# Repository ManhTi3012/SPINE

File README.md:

# S.P.I.N.E
**Stackable Power Integration & Network Electronics**

# Overview
S.P.I.N.E. is a decentralized power distribution architecture that splits control, distribution, and protection into discrete, stackable modules. Offers control and monitor over individual power rails, telemetry via CAN bus, and fault protection like over current, over voltage(due to back EMF), emergency stop.

# System Architecture
The system is composed of three primary module types, functioning analogously to a biological nervous system:

## 1. Cortex (Main Control Unit)
The Cortex is responsible for high-level decision-making and external communication.

- Bus Monitoring: Continuously monitors the main bus voltage.

- Orchestration: Controls the state of all connected Vertebra modules via RS485.

- Telemetry: Send internal system data to the external robot controller via CAN Bus.

## 2. Vertebra (Power Distribution & Switching)
Each Vertebra acts as an intelligent Power Distribution Unit (PDU).

- Distribution: Takes 1 main input and splits it into 3 protected outputs.

- Protection Topology: Utilizes a back-to-back switching topology to enable full bidirectional cutoff.

- Soft Start: Integrated Precharge circuit to prevent inrush current spikes during startup.

- Sensing: Real-time current and voltage sensing on outputs.

- Fault Propagation:

  - Local: Can autonomously cut power upon detecting over-current events.
  
  - Global: A "Critical Fault" in one Vertebra triggers a system-wide shutdown to protect the rest of the hardware.

## 3. Disc (Brake Chopper)
A purely hardware-based protection module.

- Function: Dissipates dangerous back-EMF (voltage spikes) generated by motors during rapid deceleration.

- Mechanism: A fast analog comparator circuit to trigger a dump load when voltage exceeds a set threshold.

- Zero-Latency: No microcontroller or software intervention required; purely reactive hardware protection.

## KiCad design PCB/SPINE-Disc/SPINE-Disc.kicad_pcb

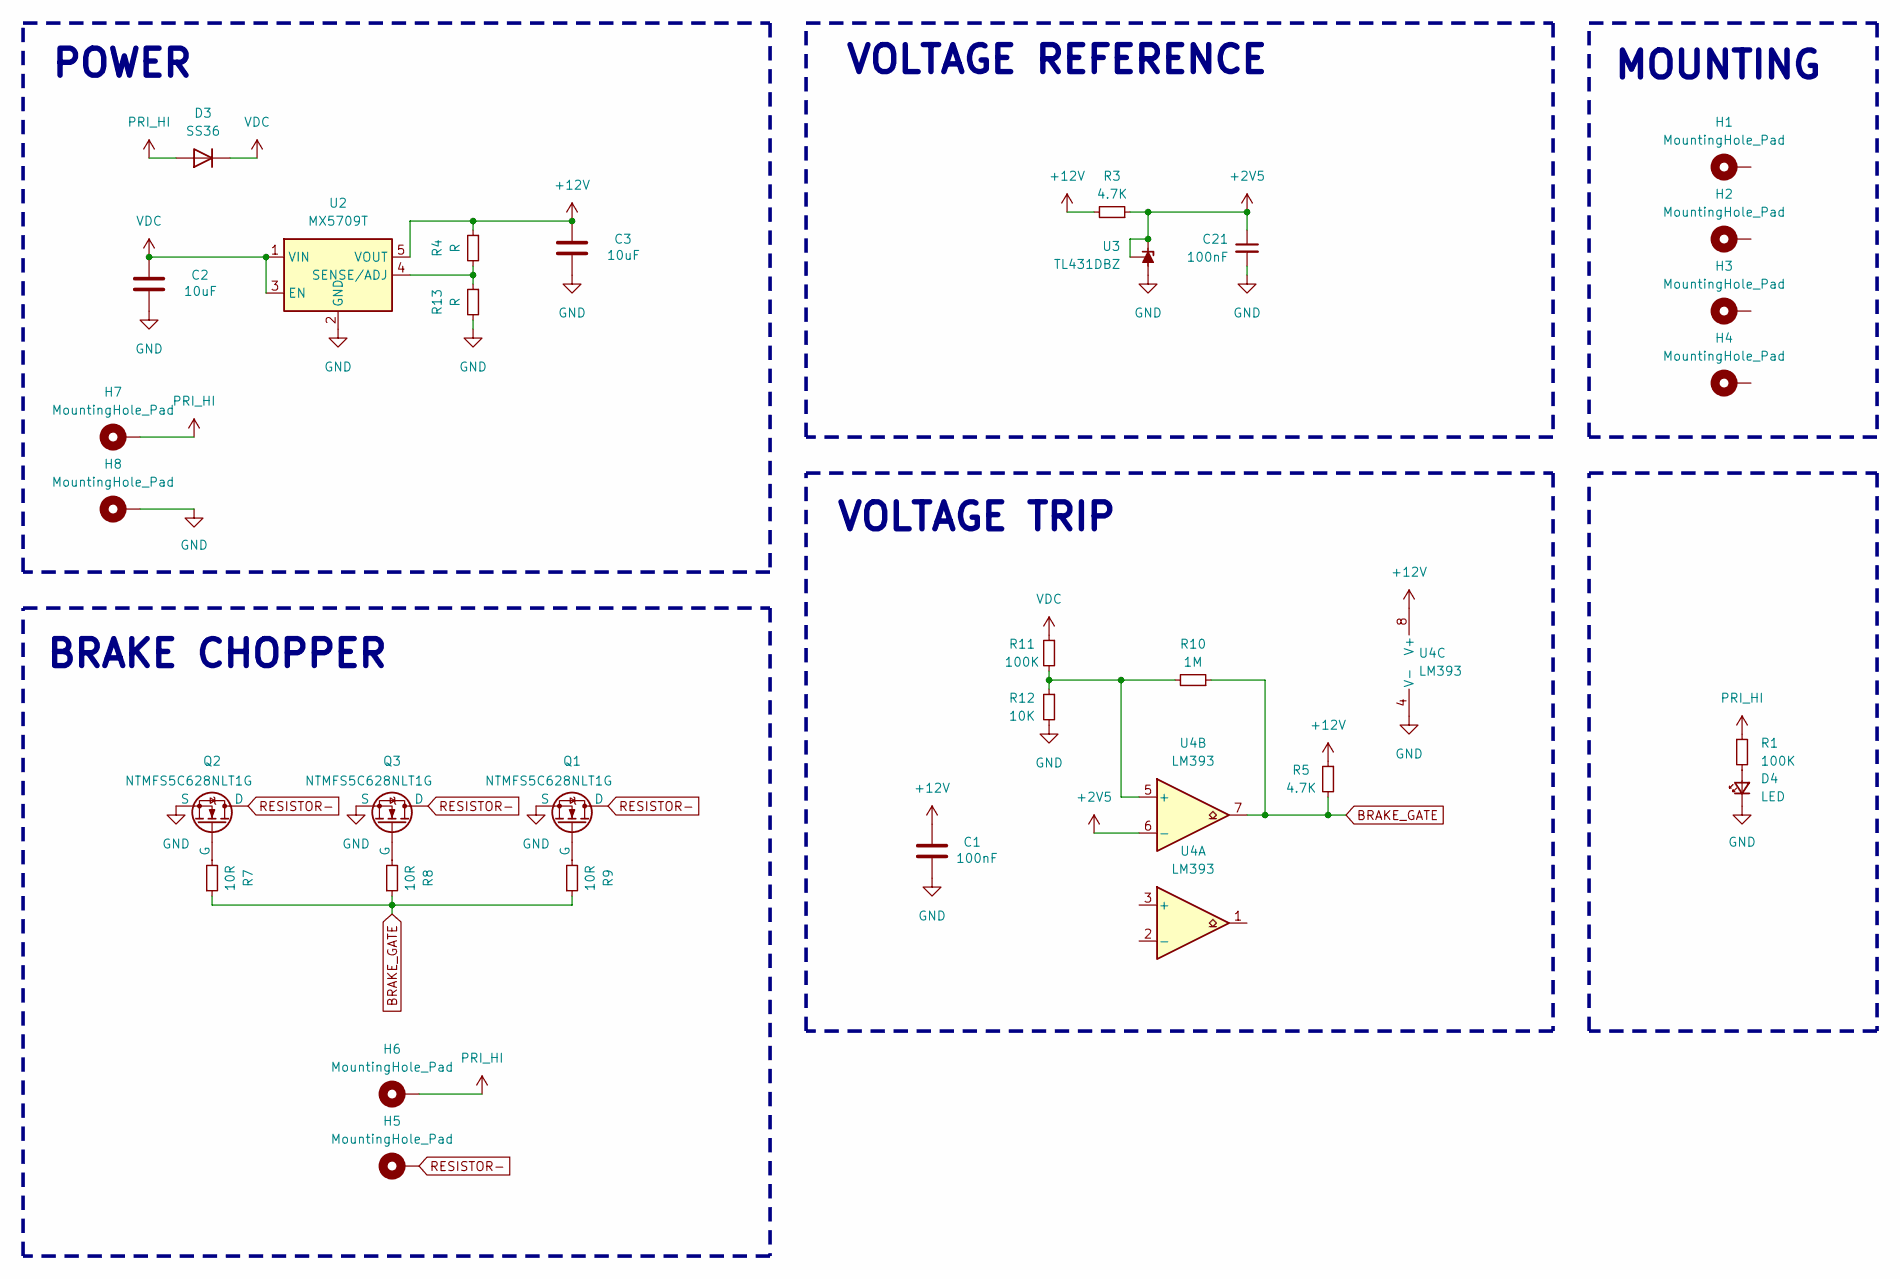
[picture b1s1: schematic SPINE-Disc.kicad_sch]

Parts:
C1: 100nF; C_0805_2012Metric
C2, C3: 10uF; C_1206_3216Metric
C21: 100nF; C_0603_1608Metric
D3: SS36; D_SMA
D4: LED; LED_0603_1608Metric
H1, H2, H3, H4, H5, H6, H7, H8: MountingHole_Pad; MountingHole_3.2mm_M3_Pad_Via
Q1, Q2, Q3: NTMFS5C628NLT1G; PQFN-8-EP_6x5mm_P1.27mm_Generic
R1, R11: 100K; R_0603_1608Metric
R3, R5: 4.7K; R_0603_1608Metric
R4, R13: R; R_0603_1608Metric
R7, R8, R9: 10R; R_0603_1608Metric
R10: 1M; R_0603_1608Metric
R12: 10K; R_0603_1608Metric
U2: MX5709T; TSOT-23-5
U3: TL431DBZ; SOT-23
U4: LM393; SOIC-8_3.9x4.9mm_P1.27mm

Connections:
+2V5: C21.1, R3.1, U3.1 (K), U3.2 (REF), U4.6 (-)
+12V: C1.2, C3.2, R3.2, R4.1, R5.1, U2.5 (VOUT), U4.8 (V+)
BRAKE_GATE: R5.2, R7.1, R8.1, R9.1, R10.1, U4.7
GND: C1.1, C2.1, C3.1, C21.2, D4.1 (K), H8.1, Q1.1 (S), Q1.2 (S), Q1.3 (S), Q2.1 (S), Q2.2 (S), Q2.3 (S), Q3.1 (S), Q3.2 (S), Q3.3 (S), R12.2, R13.2, U2.2 (GND), U3.3 (A), U4.4 (V-)
unnamed: D4.2 (A), R1.2
unnamed: Q1.4 (G), R9.2
unnamed: Q2.4 (G), R7.2
unnamed: Q3.4 (G), R8.2
unnamed: R4.2, R13.1, U2.4 (SENSE/ADJ)
unnamed: R10.2, R11.2, R12.1, U4.5 (+)
PRI_HI: D3.2 (A), H6.1, H7.1, R1.1
RESISTOR-: H5.1, Q1.5 (D), Q2.5 (D), Q3.5 (D)
VDC: C2.2, D3.1 (K), R11.1, U2.1 (VIN), U2.3 (EN)

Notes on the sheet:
VOLTAGE TRIP
VOLTAGE REFERENCE
POWER
BRAKE CHOPPER
MOUNTING

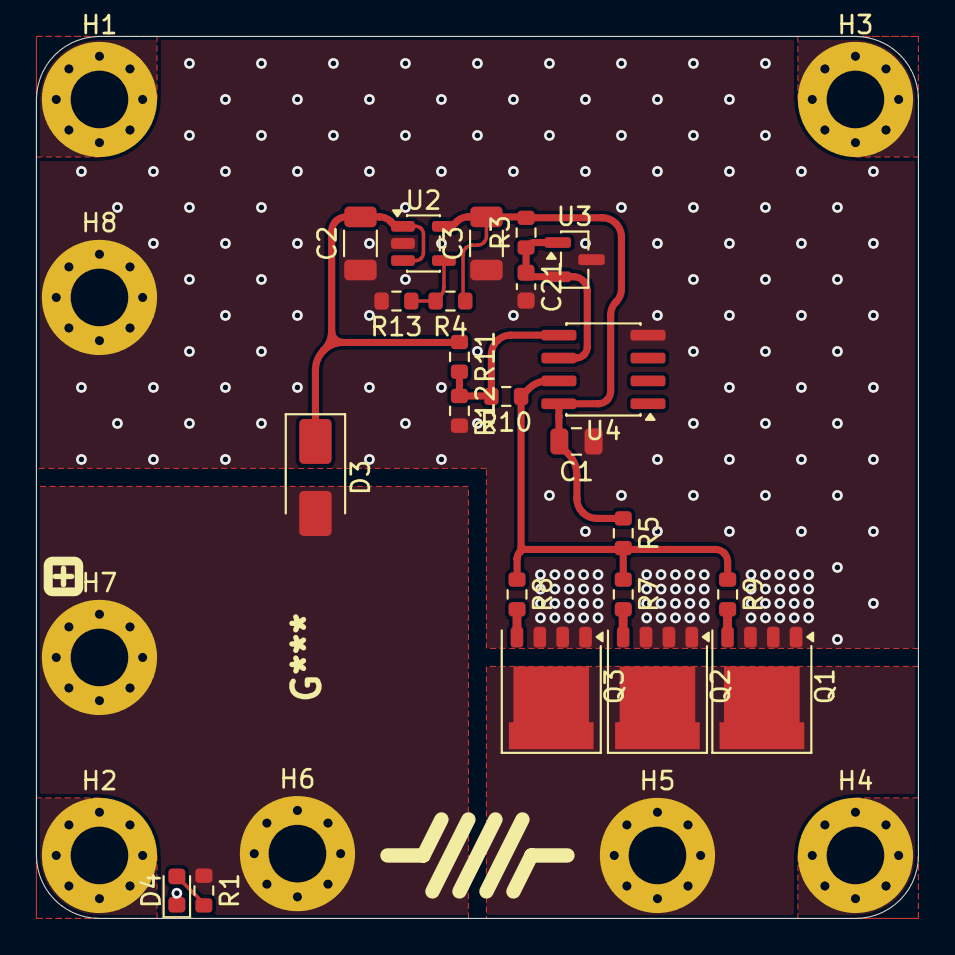
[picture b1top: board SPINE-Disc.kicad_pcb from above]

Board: 2 copper layers, 49.0 x 49.0 mm, 31 parts (0 on the bottom side), 13 nets.

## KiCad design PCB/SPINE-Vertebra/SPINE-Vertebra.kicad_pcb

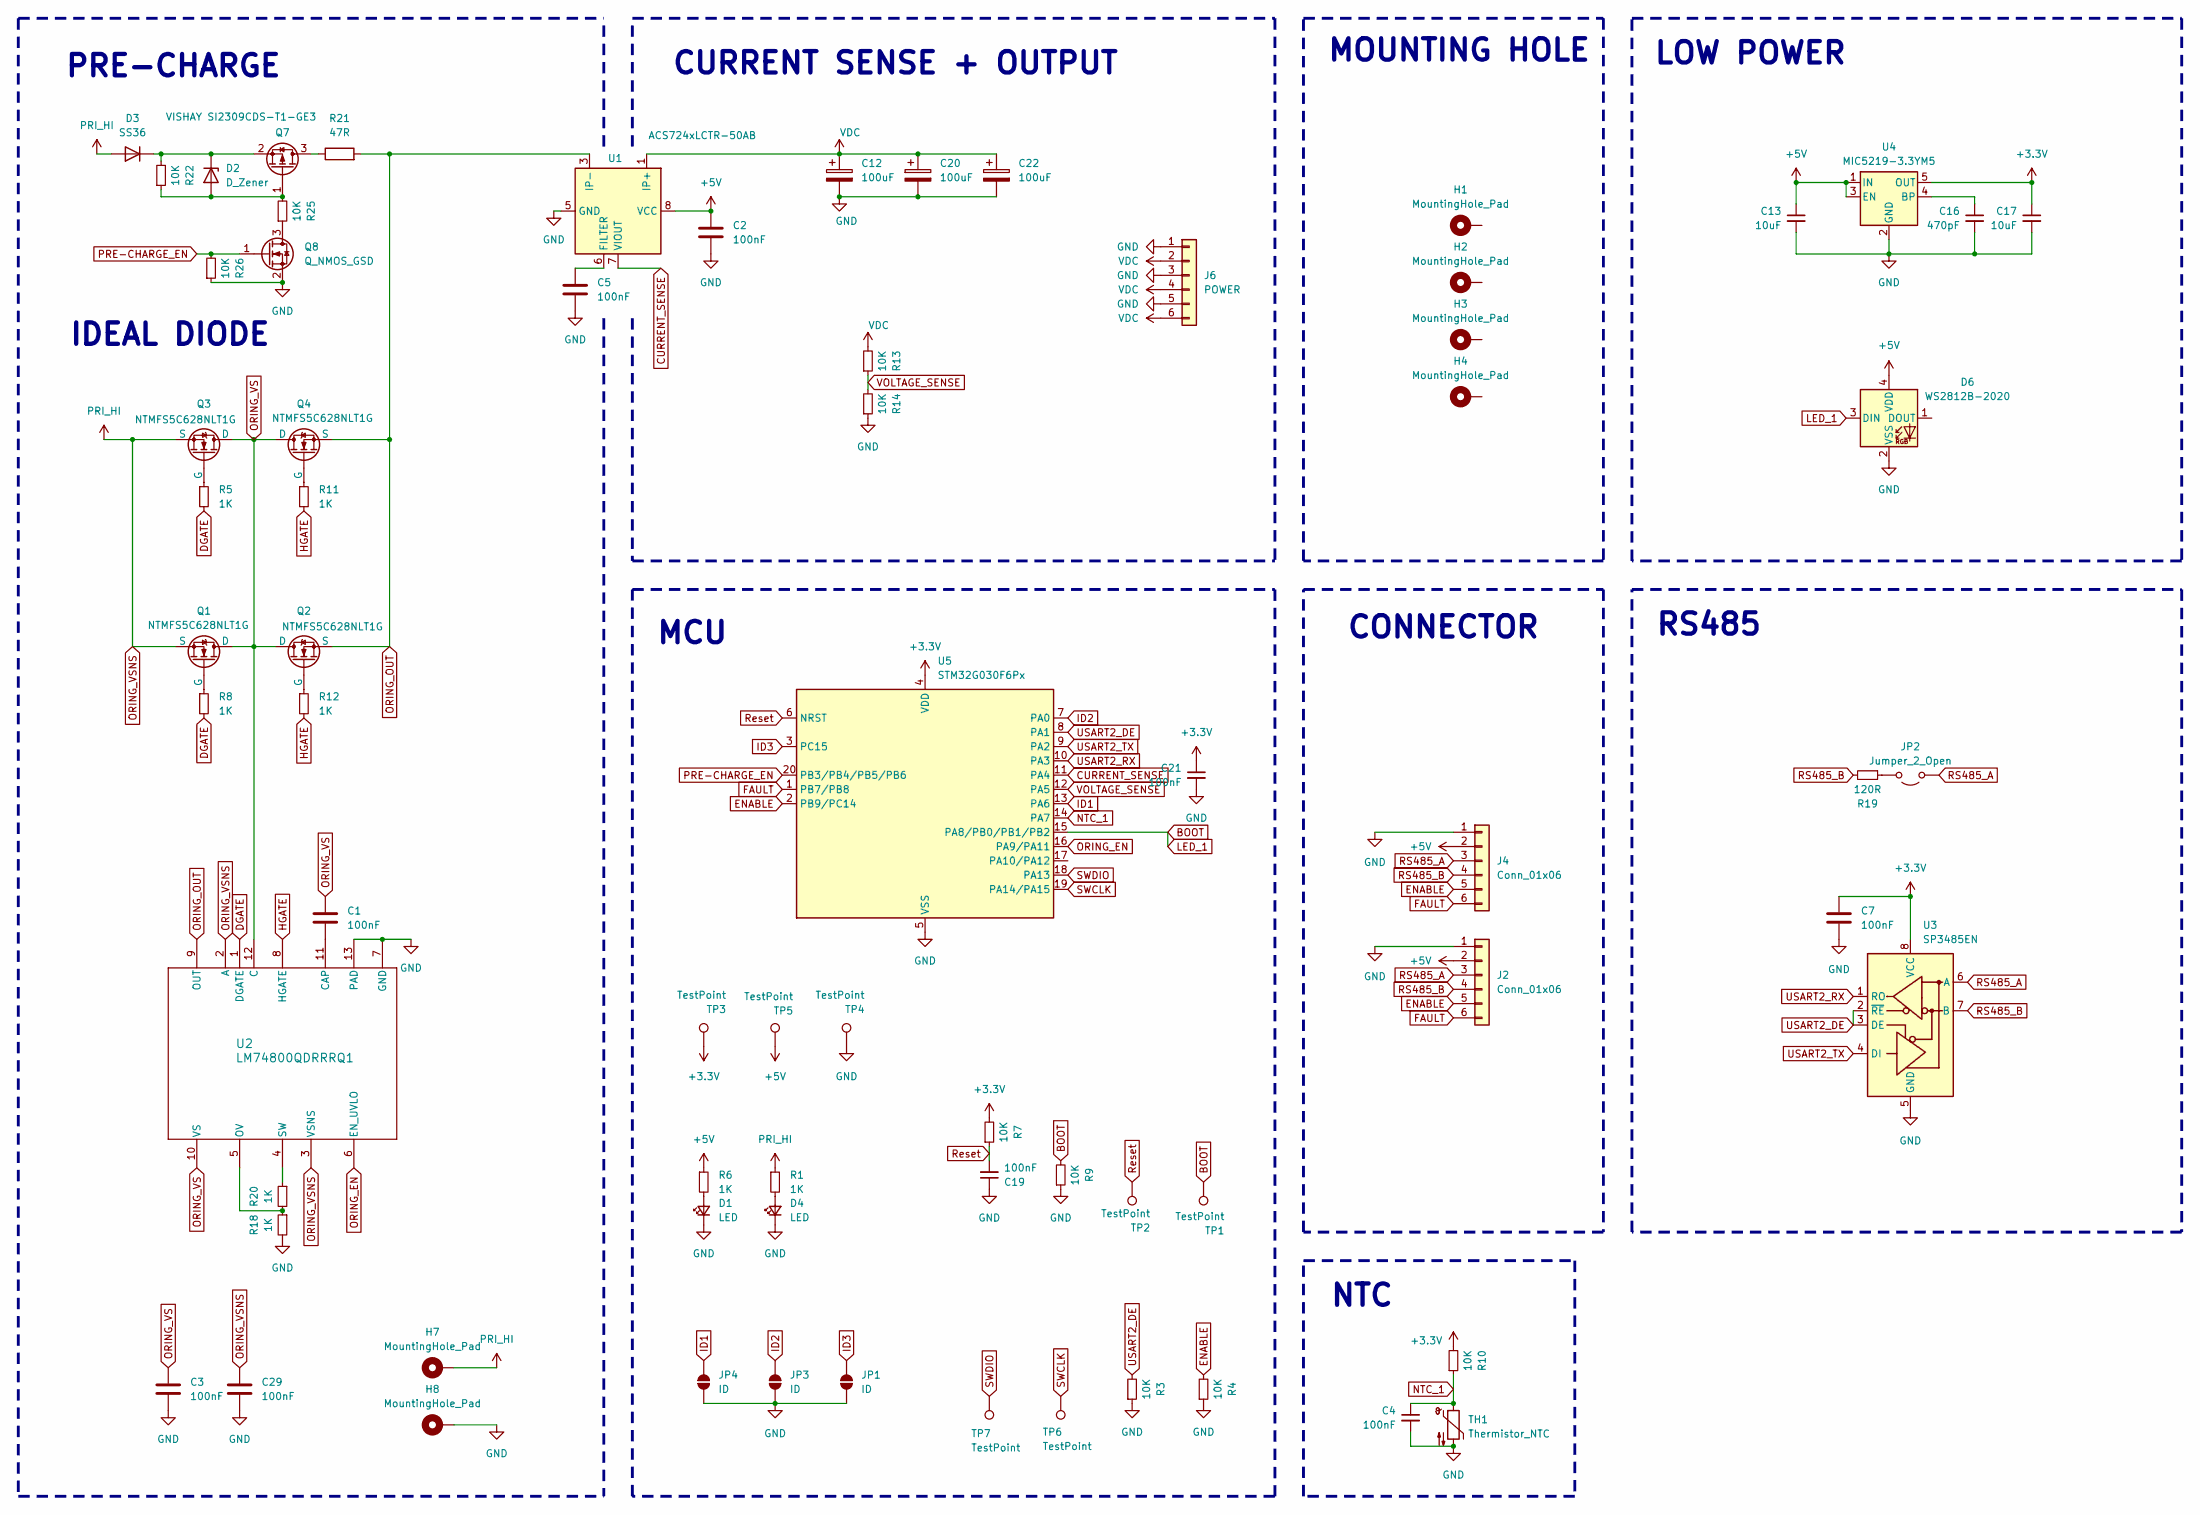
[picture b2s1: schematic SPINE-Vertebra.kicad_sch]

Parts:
C1, C2, C3, C4, C5, C7, C19, C21, C29: 100nF; C_0603_1608Metric
C12, C20, C22: 100uF; CP_Radial_D10.0mm_P5.00mm
C13, C17: 10uF; C_0603_1608Metric
C16: 470pF; C_0603_1608Metric
D1, D4: LED; LED_0603_1608Metric
D2: D_Zener; D_SOD-323
D3: SS36; D_SMA
D6: WS2812B-2020; LED_WS2812B-2020_PLCC4_2.0x2.0mm
H1, H2, H3, H4, H7, H8: MountingHole_Pad; MountingHole_3.2mm_M3_Pad_Via
J2, J4: Conn_01x06; JST_GH_SM06B-GHS-TB_1x06-1MP_P1.25mm_Horizontal
J6: POWER; TerminalBlock_MetzConnect_Type094_RT03506HBLU_1x06_P5.00mm_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
JP1, JP3, JP4: ID; SolderJumper-2_P1.3mm_Open_TrianglePad1.0x1.5mm
JP2: Jumper_2_Open; SolderJumper-2_P1.3mm_Open_RoundedPad1.0x1.5mm
Q1, Q2, Q3, Q4: NTMFS5C628NLT1G; PQFN-8-EP_6x5mm_P1.27mm_Generic
Q7: VISHAY SI2309CDS-T1-GE3; SOT-23
Q8: Q_NMOS_GSD; SOT-23
R1, R5, R6, R8, R11, R12, R18, R20: 1K; R_0603_1608Metric
R3, R4, R7, R9, R10, R13, R14, R22, R25, R26: 10K; R_0603_1608Metric
R19: 120R; R_0603_1608Metric
R21: 47R; TE-Connect_SM-Series
TH1: Thermistor_NTC; R_0603_1608Metric
TP1, TP2, TP3, TP4, TP5, TP6, TP7: TestPoint; TestPoint_Pad_D1.0mm
U1: ACS724xLCTR-50AB; SOIC-8_3.9x4.9mm_P1.27mm
U2: LM74800QDRRRQ1; DRR0012E
U3: SP3485EN; SOIC-8_3.9x4.9mm_P1.27mm
U4: MIC5219-3.3YM5; SOT-23-5
U5: STM32G030F6Px; TSSOP-20_4.4x6.5mm_P0.65mm

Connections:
+3.3V: C7.2, C17.1, C21.1, R7.2, R10.2, TP3.1, U3.8 (VCC), U4.5 (OUT), U5.4 (VDD)
+5V: C2.2, C13.1, D6.4 (VDD), J2.2, J4.2, R6.1, TP5.1, U1.8 (VCC), U4.1 (IN), U4.3 (EN)
BOOT: D6.3 (DIN), R9.2, TP1.1, U5.15 (PA8/PB0/PB1/PB2)
CURRENT_SENSE: U1.7 (VIOUT), U5.11 (PA4)
DGATE: R5.2, R8.2, U2.1 (DGATE)
ENABLE: J2.5, J4.5, R4.2, U5.2 (PB9/PC14)
FAULT: J2.6, J4.6, U5.1 (PB7/PB8)
GND: C2.1, C3.1, C4.2, C5.1, C7.1, C12.2, C13.2, C16.2, C17.2, C19.1, C20.2, C21.2, C22.2, C29.1, D1.1 (K), D4.1 (K), D6.2 (VSS), H8.1, J2.1, J4.1, J6.1, J6.3, J6.5, JP1.2 (B), JP3.2 (B), JP4.2 (B), Q8.2 (S), R3.1, R4.1, R9.1, R14.1, R18.2, R26.1, TH1.2, TP4.1, U1.5 (GND), U2.7 (GND), U2.13 (PAD), U3.5 (GND), U4.2 (GND), U5.5 (VSS)
HGATE: R11.2, R12.2, U2.8 (HGATE)
ID1: JP4.1 (A), U5.13 (PA6)
ID2: JP3.1 (A), U5.7 (PA0)
ID3: JP1.1 (A), U5.3 (PC15)
NTC_1: C4.1, R10.1, TH1.1, U5.14 (PA7)
unnamed: D1.2 (A), R6.2
unnamed: D2.2 (A), Q7.1 (G), R22.1, R25.2
unnamed: D2.1 (K), D3.1 (K), Q7.2 (S), R22.2
unnamed: D4.2 (A), R1.2
unnamed: JP2.2 (B), R19.1
unnamed: Q1.4 (G), R8.1
unnamed: Q2.4 (G), R12.1
unnamed: Q3.4 (G), R5.1
unnamed: Q4.4 (G), R11.1
unnamed: Q7.3 (D), R21.1
unnamed: Q8.3 (D), R25.1
unnamed: C5.2, U1.6 (FILTER)
unnamed: C1.1, U2.11 (CAP)
unnamed: R18.1, R20.2, U2.5 (OV)
unnamed: R20.1, U2.4 (SW)
unnamed: C16.1, U4.4 (BP)
ORING_EN: U2.6 (EN_UVLO), U5.16 (PA9/PA11)
ORING_OUT: Q2.1 (S), Q2.2 (S), Q2.3 (S), Q4.1 (S), Q4.2 (S), Q4.3 (S), R21.2, U1.3 (IP-), U1.4 (IP-), U2.9 (OUT)
ORING_VS: C1.2, C3.2, Q1.5 (D), Q2.5 (D), Q3.5 (D), Q4.5 (D), U2.10 (VS), U2.12 (C)
ORING_VSNS: C29.2, D3.2 (A), H7.1, Q1.1 (S), Q1.2 (S), Q1.3 (S), Q3.1 (S), Q3.2 (S), Q3.3 (S), R1.1, U2.2 (A), U2.3 (VSNS)
PRE-CHARGE_EN: Q8.1 (G), R26.2, U5.20 (PB3/PB4/PB5/PB6)
RS485_A: J2.3, J4.3, JP2.1 (A), U3.6 (A)
RS485_B: J2.4, J4.4, R19.2, U3.7 (B)
Reset: C19.2, R7.1, TP2.1, U5.6 (NRST)
SWCLK: TP6.1, U5.19 (PA14/PA15)
SWDIO: TP7.1, U5.18 (PA13)
USART2_DE: R3.2, U3.2 (~RE), U3.3 (DE), U5.8 (PA1)
USART2_RX: U3.1 (RO), U5.10 (PA3)
USART2_TX: U3.4 (DI), U5.9 (PA2)
VDC: C12.1, C20.1, C22.1, J6.2, J6.4, J6.6, R13.2, U1.1 (IP+), U1.2 (IP+)
VOLTAGE_SENSE: R13.1, R14.2, U5.12 (PA5)

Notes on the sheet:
MOUNTING HOLE
CONNECTOR
IDEAL DIODE
MCU
RS485
LOW POWER
PRE-CHARGE
CURRENT SENSE + OUTPUT
NTC

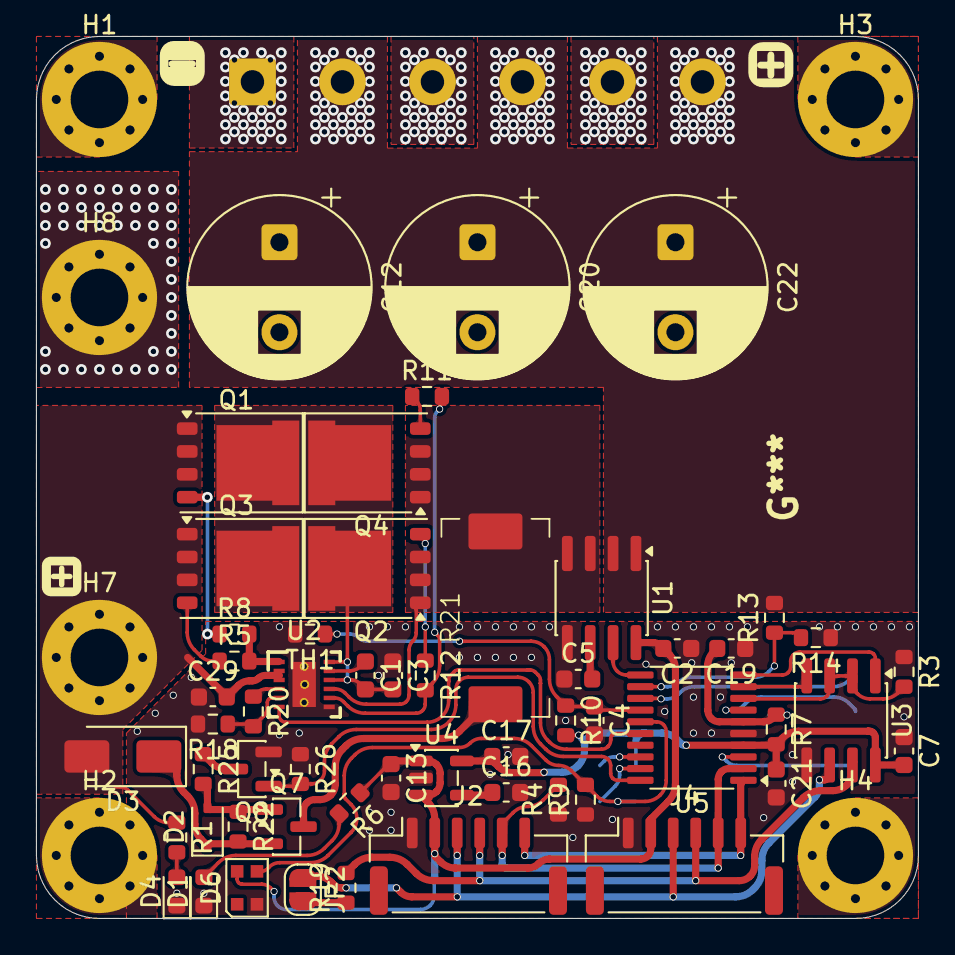
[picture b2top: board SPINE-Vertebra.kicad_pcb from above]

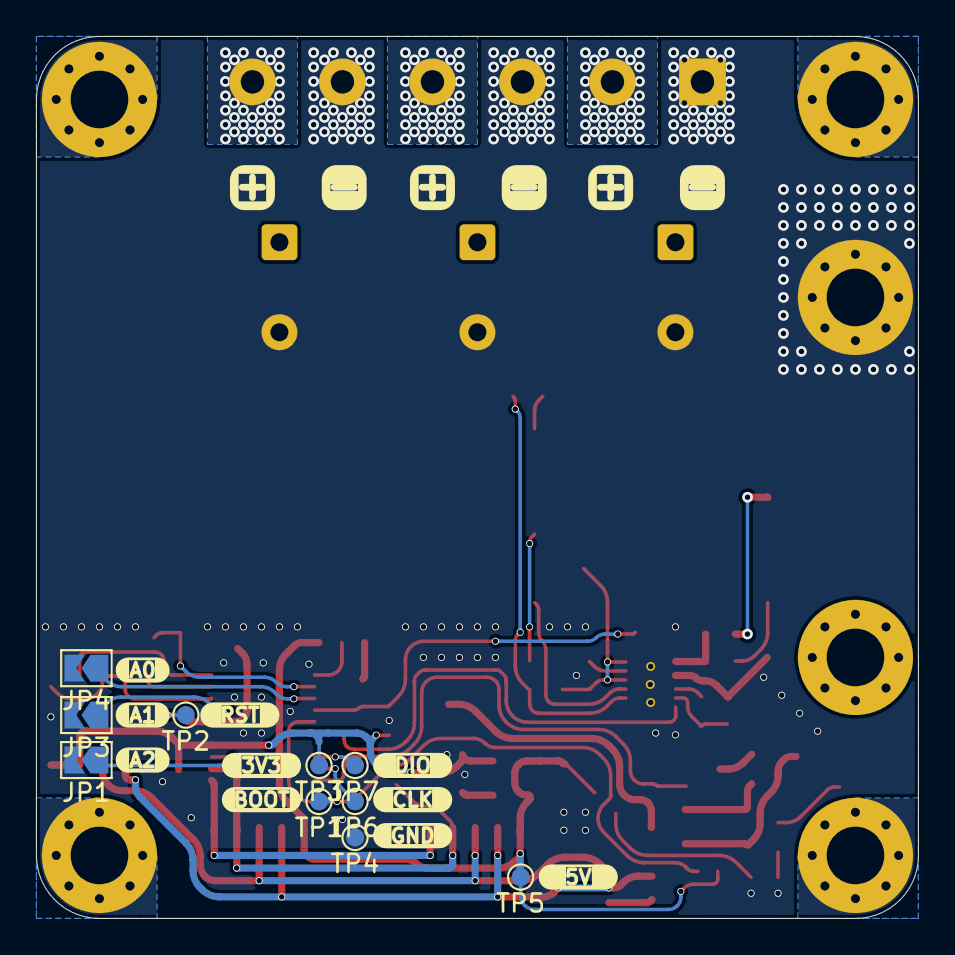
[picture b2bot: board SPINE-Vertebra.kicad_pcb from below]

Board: 2 copper layers, 49.0 x 49.0 mm, 72 parts (10 on the bottom side), 44 nets.

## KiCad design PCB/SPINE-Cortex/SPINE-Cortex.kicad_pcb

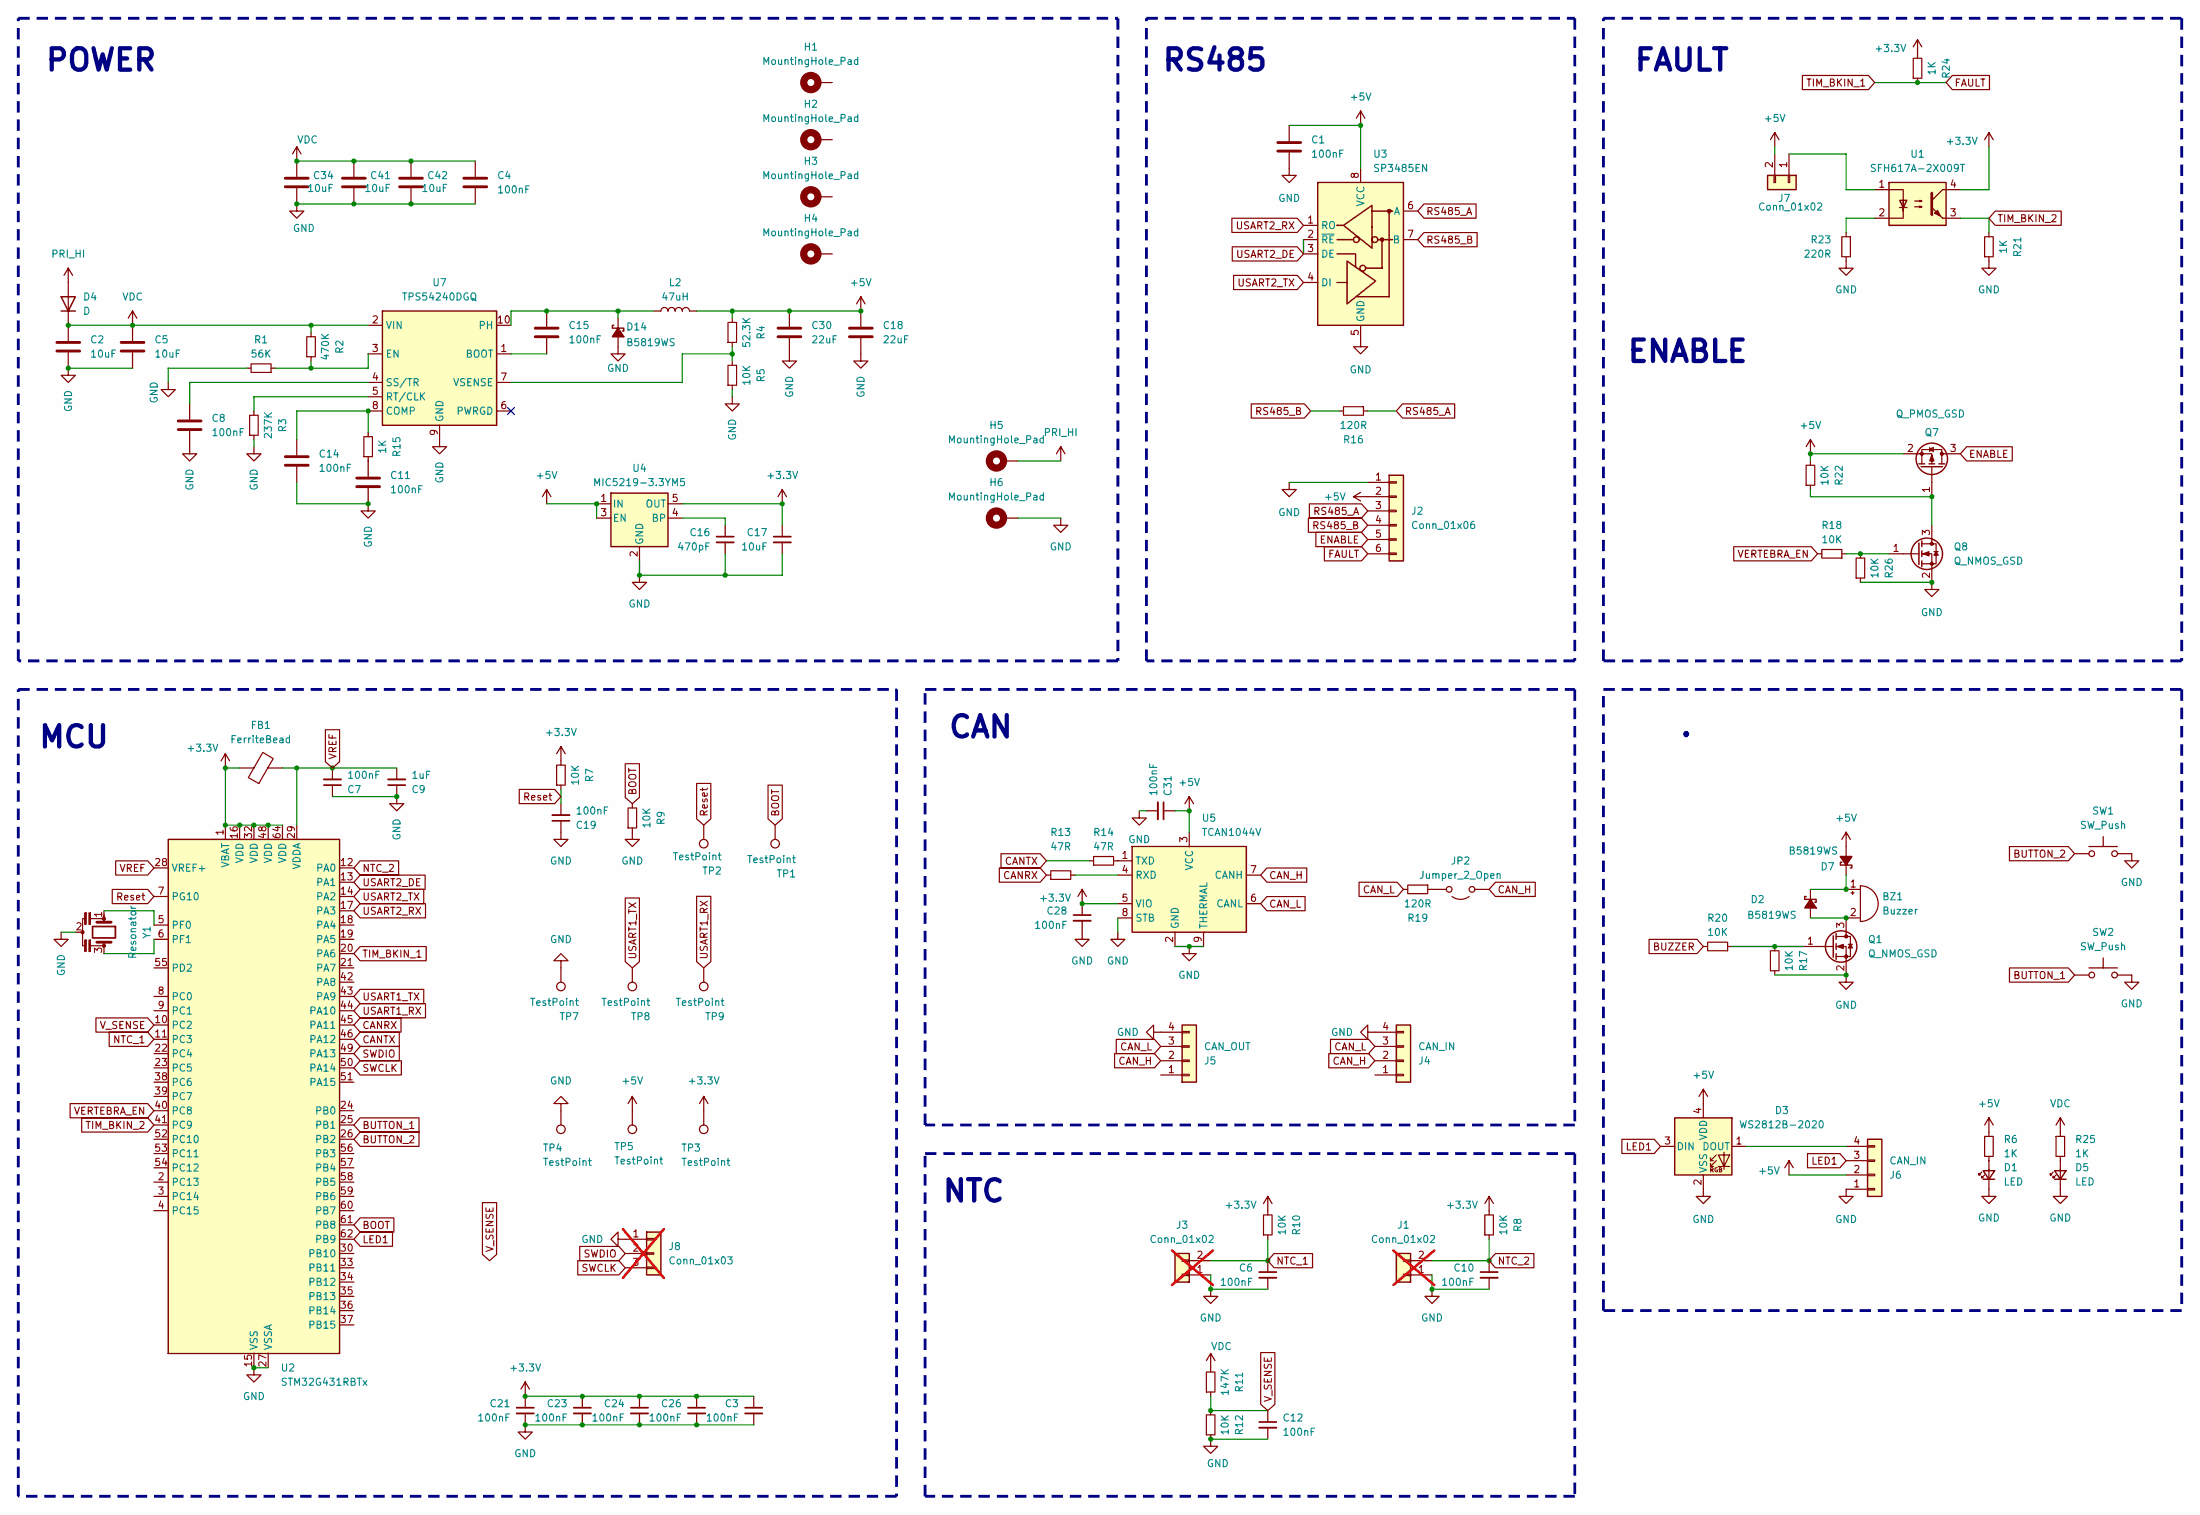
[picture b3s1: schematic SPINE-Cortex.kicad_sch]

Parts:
BZ1: Buzzer; MagneticBuzzer_CUI_CMT-8504-100-SMT
C1, C3, C4, C6, C7, C8, C10, C11, C12, C14, C15, C19, C21, C23, C24, C26, C28, C31: 100nF; C_0603_1608Metric
C2, C5, C34, C41, C42: 10uF; C_1206_3216Metric
C9: 1uF; C_0603_1608Metric
C16: 470pF; C_0603_1608Metric
C17: 10uF; C_0603_1608Metric
C18, C30: 22uF; C_0805_2012Metric
D1, D5: LED; LED_0603_1608Metric
D2, D7, D14: B5819WS; D_0805_2012Metric
D3: WS2812B-2020; LED_WS2812B-2020_PLCC4_2.0x2.0mm
D4: D; D_SMA
FB1: FerriteBead; L_0603_1608Metric
H1, H2, H3, H4, H5, H6: MountingHole_Pad; MountingHole_3.2mm_M3_Pad_Via
J1, J3: Conn_01x02; PinHeader_1x02_P2.54mm_Vertical; not fitted
J2: Conn_01x06; JST_GH_SM06B-GHS-TB_1x06-1MP_P1.25mm_Horizontal
J4, J6: CAN_IN; JST_GH_SM04B-GHS-TB_1x04-1MP_P1.25mm_Horizontal
J5: CAN_OUT; JST_GH_SM04B-GHS-TB_1x04-1MP_P1.25mm_Horizontal
J7: Conn_01x02; TerminalBlock_MetzConnect_Type094_RT03502HBLU_1x02_P5.00mm_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
J8: Conn_01x03; PinHeader_1x03_P2.54mm_Vertical; not fitted
JP2: Jumper_2_Open; SolderJumper-2_P1.3mm_Open_RoundedPad1.0x1.5mm
L2: 47uH; L_APV_ANR4020
Q1, Q8: Q_NMOS_GSD; SOT-23
Q7: Q_PMOS_GSD; SOT-23
R1: 56K; R_0603_1608Metric
R2: 470K; R_0603_1608Metric
R3: 237K; R_0603_1608Metric
R4: 52.3K; R_0603_1608Metric
R5, R7, R8, R9, R10, R12, R17, R18, R20, R22, R26: 10K; R_0603_1608Metric
R6, R15, R21, R24, R25: 1K; R_0603_1608Metric
R11: 147K; R_0603_1608Metric
R13, R14: 47R; R_0603_1608Metric
R16, R19: 120R; R_0603_1608Metric
R23: 220R; R_0603_1608Metric
SW1, SW2: SW_Push; SW_SPST_B3S-1000
TP1, TP2, TP3, TP4, TP5, TP7, TP8, TP9: TestPoint; TestPoint_Pad_D1.0mm
U1: SFH617A-2X009T; SMDIP-4_W9.53mm_Clearance8mm
U2: STM32G431RBTx; LQFP-64_10x10mm_P0.5mm
U3: SP3485EN; SOIC-8_3.9x4.9mm_P1.27mm
U4: MIC5219-3.3YM5; SOT-23-5
U5: TCAN1044V; Texas_S-PVSON-N8
U7: TPS54240DGQ; HVSSOP-10-1EP_3x3mm_P0.5mm_EP1.57x1.88mm_ThermalVias
Y1: Resonator; Resonator_SMD_Murata_CSTxExxV-3Pin_3.0x1.1mm

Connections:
+3.3V: C3.1, C17.1, C21.1, C23.1, C24.1, C26.1, C28.1, FB1.1, R7.2, R8.2, R10.2, R24.2, TP3.1, U1.4, U2.1 (VBAT), U2.16 (VDD), U2.32 (VDD), U2.48 (VDD), U2.64 (VDD), U4.5 (OUT), U5.5 (VIO)
+5V: C1.2, C18.2, C30.2, C31.1, D3.4 (VDD), D7.2 (A), J2.2, J6.2, J7.2, L2.2, Q7.2 (S), R4.2, R6.1, R22.2, TP5.1, U3.8 (VCC), U4.1 (IN), U4.3 (EN), U5.3 (VCC)
BOOT: R9.2, TP1.1, U2.61 (PB8)
BUTTON_1: SW2.1, U2.25 (PB1)
BUTTON_2: SW1.1, U2.26 (PB2)
BUZZER: R20.2
CANRX: R13.1, U2.45 (PA11)
CANTX: R14.1, U2.46 (PA12)
CAN_H: J4.2, J5.2, JP2.1 (A), U5.7 (CANH)
CAN_L: J4.3, J5.3, R19.2, U5.6 (CANL)
ENABLE: J2.5, Q7.3 (D)
FAULT: J2.6, R24.1, U2.20 (PA6)
GND: C1.1, C2.1, C3.2, C4.1, C5.1, C6.2, C7.1, C8.1, C9.1, C10.2, C11.1, C12.2, C14.1, C16.2, C17.2, C18.1, C19.1, C21.2, C23.2, C24.2, C26.2, C28.2, C30.1, C31.2, C34.1, C41.1, C42.1, D1.1 (K), D3.2 (VSS), D5.1 (K), D14.2 (A), H6.1, J1.1, J2.1, J3.1, J4.4, J5.4, J6.1, J8.1, Q1.2 (S), Q8.2 (S), R1.2, R3.1, R5.1, R9.1, R12.1, R17.1, R21.1, R23.2, R26.1, SW1.2, SW2.2, TP4.1, TP7.1, U2.15 (VSS), U2.27 (VSSA), U2.31 (VSS), U2.47 (VSS), U2.63 (VSS), U3.5 (GND), U4.2 (GND), U5.2 (GND), U5.8 (STB), U5.9 (THERMAL), U7.9 (GND), U7.11 (GND), Y1.2
LED1: D3.3 (DIN), J6.3, U2.62 (PB9)
NTC_1: C6.1, J3.2, R10.1, U2.11 (PC3)
NTC_2: C10.1, J1.2, R8.1, U2.12 (PA0)
unnamed: BZ1.1 (+), D2.1 (K), D7.1 (K)
unnamed: BZ1.2 (-), D2.2 (A), Q1.3 (D)
unnamed: C11.2, R15.1
unnamed: D1.2 (A), R6.2
unnamed: D3.1 (DOUT), J6.4
unnamed: D5.2 (A), R25.2
unnamed: C15.2, D14.1 (K), L2.1, U7.10 (PH)
unnamed: J7.1, U1.1
unnamed: JP2.2 (B), R19.1
unnamed: Q1.1 (G), R17.2, R20.1
unnamed: Q7.1 (G), Q8.3 (D), R22.1
unnamed: Q8.1 (G), R18.1, R26.2
unnamed: R23.1, U1.2
unnamed: U2.5 (PF0), Y1.1
unnamed: U2.6 (PF1), Y1.3
unnamed: C16.1, U4.4 (BP)
unnamed: R13.2, U5.4 (RXD)
unnamed: R14.2, U5.1 (TXD)
unnamed: C15.1, U7.1 (BOOT)
unnamed: C14.2, R15.2, U7.8 (COMP)
unnamed: R1.1, R2.1, U7.3 (EN)
unnamed: R3.2, U7.5 (RT/CLK)
unnamed: C8.2, U7.4 (SS/TR)
unnamed: R4.1, R5.2, U7.7 (VSENSE)
PRI_HI: D4.2 (A), H5.1
RS485_A: J2.3, R16.1, U3.6 (A)
RS485_B: J2.4, R16.2, U3.7 (B)
Reset: C19.2, R7.1, TP2.1, U2.7 (PG10)
SWCLK: J8.3, U2.50 (PA14)
SWDIO: J8.2, U2.49 (PA13)
TIM_BKIN_2: R21.2, U1.3, U2.41 (PC9)
USART1_RX: TP9.1, U2.44 (PA10)
USART1_TX: TP8.1, U2.43 (PA9)
USART2_DE: U2.13 (PA1), U3.2 (~RE), U3.3 (DE)
USART2_RX: U2.17 (PA3), U3.1 (RO)
USART2_TX: U2.14 (PA2), U3.4 (DI)
VDC: C2.2, C4.2, C5.2, C34.2, C41.2, C42.2, D4.1 (K), R2.2, R11.2, R25.1, U7.2 (VIN)
VERTEBRA_EN: R18.2, U2.40 (PC8)
VREF: C7.2, C9.2, FB1.2, U2.28 (VREF+), U2.29 (VDDA)
V_SENSE: C12.1, R11.1, R12.2, U2.10 (PC2)

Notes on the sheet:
CAN
FAULT
MCU
RS485
POWER
NTC
ENABLE

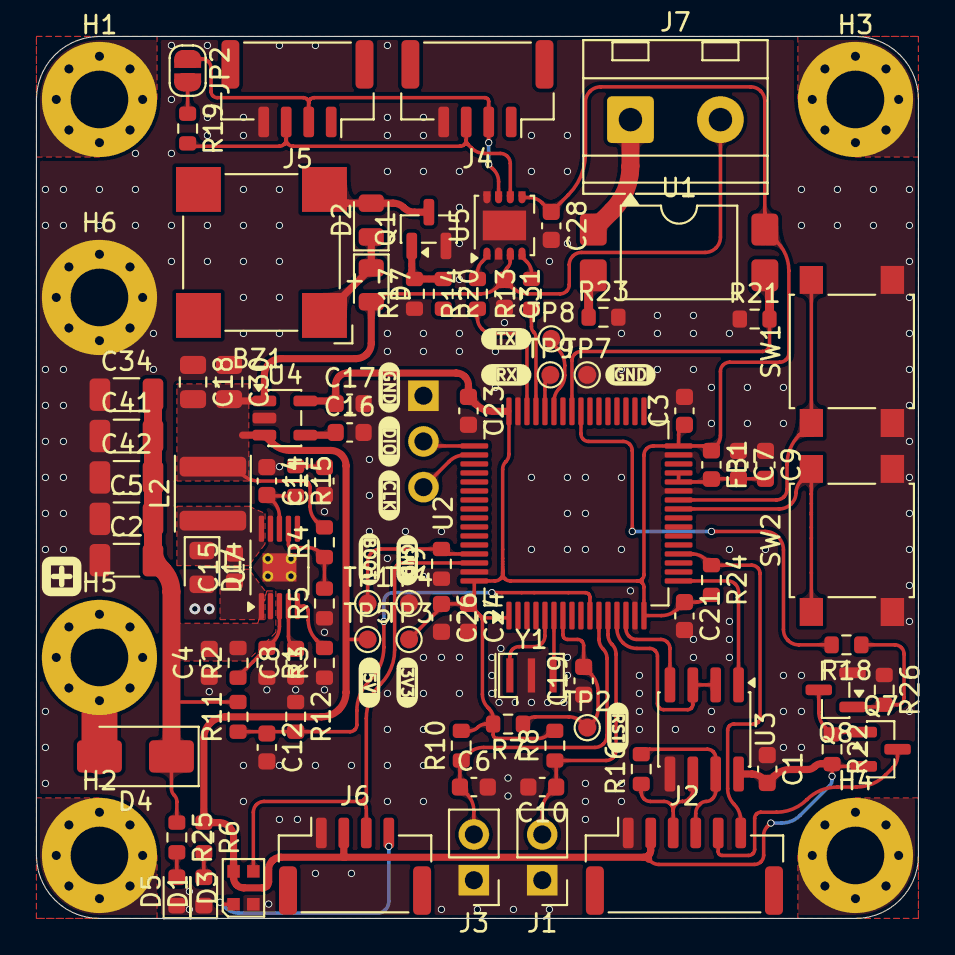
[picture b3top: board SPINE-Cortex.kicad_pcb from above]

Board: 2 copper layers, 49.0 x 49.0 mm, 99 parts (1 on the bottom side), 55 nets.

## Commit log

2025-12-08 vertebra update
2025-12-09 Finish Vertebra
2025-12-11 Vertebra fix
2025-12-13 README
    Added detailed overview and system architecture sections to the README.
2025-12-13 Clean up README.md
2025-12-13 README
